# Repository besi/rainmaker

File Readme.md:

# Rainmaker

Lets you listen to rain. That's it.

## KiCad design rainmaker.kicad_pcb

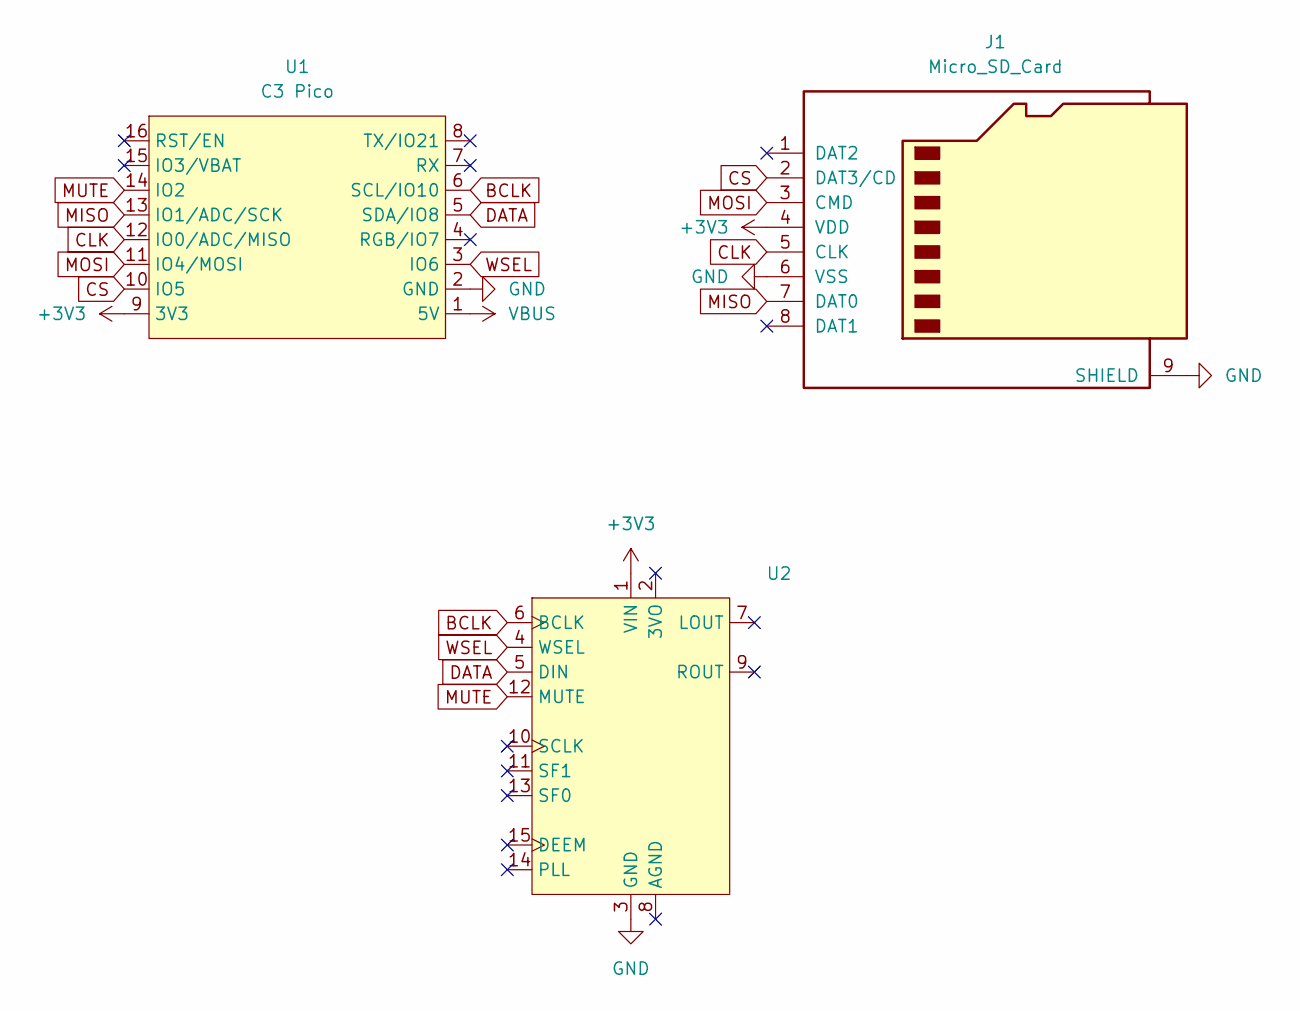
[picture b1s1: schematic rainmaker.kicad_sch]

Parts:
J1: Micro_SD_Card; sd-card
U1: C3 Pico; c3-pico
U2: uda1334

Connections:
+3V3: J1.4 (VDD), U1.9 (3V3), U2.1 (VIN)
BCLK: U1.6 (SCL/IO10), U2.6 (BCLK)
CLK: J1.5 (CLK), U1.12 (IO0/ADC/MISO)
CS: J1.2 (DAT3/CD), U1.10 (IO5)
DATA: U1.5 (SDA/IO8), U2.5 (DIN)
GND: J1.6 (VSS), J1.9 (SHIELD), U1.2 (GND), U2.3 (GND)
MISO: J1.7 (DAT0), U1.13 (IO1/ADC/SCK)
MOSI: J1.3 (CMD), U1.11 (IO4/MOSI)
MUTE: U1.14 (IO2), U2.12 (MUTE)
VBUS: U1.1 (5V)
WSEL: U1.3 (IO6), U2.4 (WSEL)

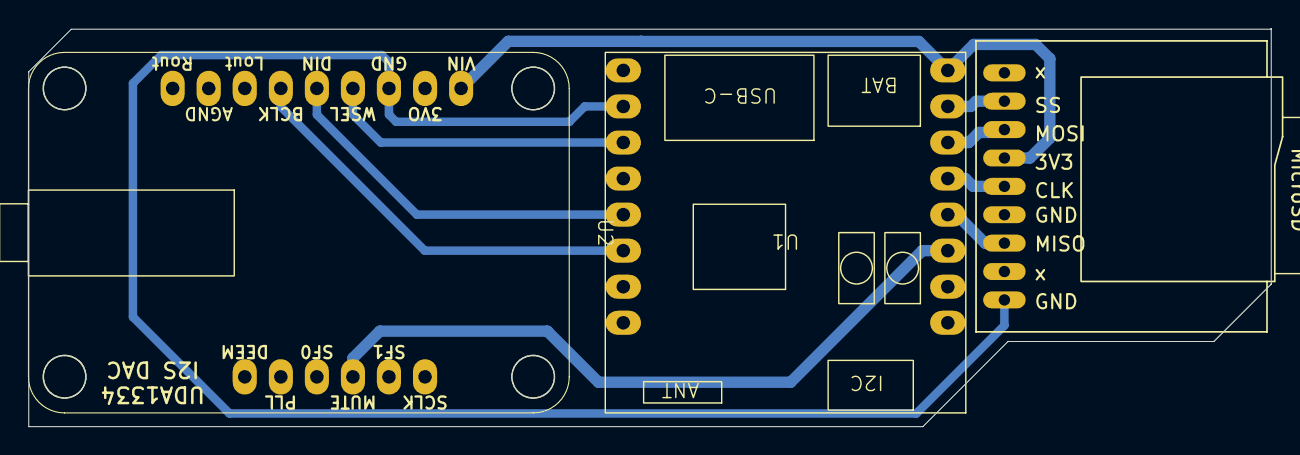
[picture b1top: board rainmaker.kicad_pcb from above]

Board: 2 copper layers, 87.5 x 28.0 mm, 3 parts (0 on the bottom side), 10 nets.
